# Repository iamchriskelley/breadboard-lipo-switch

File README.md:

#Breadboard Lipo Switch

This is a simple, breadboard friendly PCB that holds a 2-pin JST connector (right-angle), SPDT switch, and LED with resistor. Assemble it and plug in a lipo battery you have a nice switchable power supply for your next prototype circuit!

###Suggested Parts  
Switch: http://www.mouser.com/Search/ProductDetail.aspx?R=SS-12D07-VG_4_NS_GA_PAvirtualkey61110000virtualkey611-SS12D07VG4NSGAPA  
Lipo connector: http://www.mouser.com/ProductDetail/Adafruit/1769/?qs=sGAEpiMZZMsMyYRRhGMFNlCdtNxpnOUdaNxuf4VjKxc%3d  
LED: http://www.mouser.com/ProductDetail/Kingbright/APT1608EC/?qs=sGAEpiMZZMseGfSY3csMkeytxqHAv00Aff4kcuIAmaQ%3d  
Resistor: http://www.mouser.com/ProductDetail/Panasonic/ERJ-3GEYJ221V/?qs=sGAEpiMZZMvdGkrng054t8ugkoYZivkgwZ51j9iZI7w%3d

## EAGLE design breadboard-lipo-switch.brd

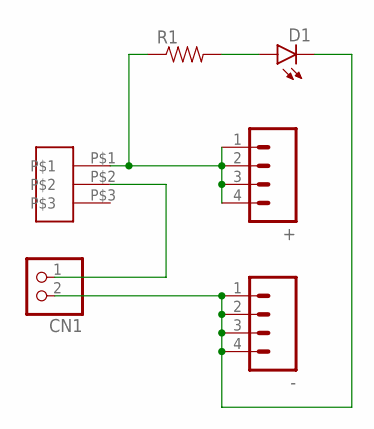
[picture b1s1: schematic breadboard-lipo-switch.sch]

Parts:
+: M04PTH; 1X04
-: M04PTH; 1X04
CN1: JST_2PIN-SMT-RA; JST-PH-2-SMT-RA
D1: LED0603; LED-0603
R1: RESISTOR0603-RES; 0603-RES
U$1: OS102-SPDT-SWITCH

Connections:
GND: -.1, -.2, -.3, -.4, CN1.2 (1), D1.C
unnamed: D1.A, R1.2
VCC: +.1, +.2, +.3, +.4, R1.1, U$1.P$1
VIN: CN1.1 (2), U$1.P$2

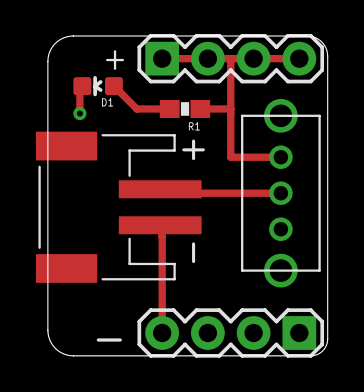
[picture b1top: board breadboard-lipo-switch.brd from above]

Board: 2 copper layers, 15.5 x 17.8 mm, 6 parts (0 on the bottom side), 4 nets.

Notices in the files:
parts and their libraries:
SparkFun-Connectors: Licensing: Creative Commons ShareAlike 4.0 International - https://creativecommons.org/licenses/by-sa/4.0
